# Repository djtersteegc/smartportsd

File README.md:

A couple PCB's I've designed to run the SmartportSD FAT code from Katherine Stark (based on the work of Robert Justice and Andrea Ottaviani) allowing you to connect a 32MB ProDOS partition to your SmartPort enabled Apple II (IIc, IIc+, IIgs). If you have a Apple IIe, solutions like a SoftSP card with you Disk II card, or something like Brad Bell's [SmartDiskII](https://github.com/btb/SmartDiskII) card will also allow hookup and usage. Yes, it works with Total Replay.

# SmartportSD Nano Shield

This is my original design.  Works best with a Duo Disk cable, but has a header to wire up a custom cable if needed.  All through hold modules, super easy build. I added some additional LED's to indicate which of the four ProDOS partitions is currently loaded.

See the [Nano Shield page](smartportsd-nano-shield/README.md) for BOM and assembly instructions.

# SmartportSD SMD

This one is a bit more of an advanced build and is based off my [Tapecart SD](https://github.com/djtersteegc/tapecart-sd-vertical) design I did for the Commodore 64. Uses a full size SD card for ease of handling and plugs in directly to the back of an Apple IIc/c+/gs.  There is a lightpipe for the activity LED and the narrow case design allows plenty of clearance for the bulkiest composite video connectors I could find in my collection.

See the [SMD page](smartport-smd/README.md) for BOM and assembly instructions.

# Getting a Board

If I have extra PCB's, they will be listed on Tindie.

https://www.tindie.com/products/tersteeg/smartportsd-apple-ii-pcb/

Otherwise, you can download the gerbers and use your favorite fab (JLCPCB, PCBWay, etc.) to make your own batch.

# Acknowledgements

Robert Justice for his original SmartPortCFA project http://www.users.on.net/~rjustice/SmartportCFA/SmartportCFA.htm

Andrea Ottaviani for his Arduino/SD port of Robert's work http://www.users.on.net/~rjustice/SmartportCFA/SmartportSD.htm

Katherine Stark for adding FAT support to Andrea's work to make it easier to manage the partitions on the SD card. https://gitlab.com/nyankat/smartportsd

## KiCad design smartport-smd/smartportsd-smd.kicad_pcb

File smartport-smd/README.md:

# BOM

There's an interactive BOM [here](https://djtersteegc.github.io/smartportsd/ibom-smd-v1.1.html), and CSV version with footprint info [here](https://djtersteegc.github.io/smartportsd/bom-smd-v1.1.csv). The interactive one is super useful when placing the SMD components.

C5 is an optional bulk capacitor for the 5V power rail near the MCU.  In my experience building these it is not needed.

The SD card connector is commonly available from several different Chinese suppliers and often called "long body", "non popping", or "push pull" on AliExpress or eBay.

https://www.aliexpress.us/item/3256805779248826.html

Here's some links on LCSC.

https://www.lcsc.com/product-detail/SD-Card-Connectors_Hanbo-Electronic-SD-112_C961673.html

https://www.lcsc.com/product-detail/SD-Card-Connectors_XUNPU-SD-102_C266602.html

https://www.lcsc.com/product-detail/SD-Card-Connectors_Megastar-ZX-SD-282-8Y_C7419835.html

It should also cross with a Wurth 693063010911 or AMP GSD090012SEU if you want something domestically.

The pins for the DB19 connector can be purchased from this seller on AliExpress,  https://www.aliexpress.us/item/3256802431271655.html Ideally I would have used the "PCB Plug" model if they stocked them which are similar to the TE/AMP 5-745287-4 model mozzwald used on the [FujiApple DB19 to IDC20 adapters](https://github.com/FujiNetWIFI/fujinet-hardware/tree/master/AppleII/DB-19M-Adapter), but these are much more cost effective and work just as well once assembled.

# Case

The case was created in DesignSpark and the design file is available if you would like to modify it further.

There is a single light pipe that should be printed in transparent material, or you can just leave it off completely. The case is designed to be printed at 0.2mm layer heights and assembled with two M2.5x14mm screws through the connector body and two M2.5 nuts pushed into either the handle or lid.

# Assembly

Assemble all the SMD components.  I use solder paste hand applied with a pneumatic dispenser and then finish on a hot plate. But you can also hand solder, use hot air, or even order a stencil for paste application and use a proper reflow oven. I use a red LED for the activity indicator. Make sure to observe polarity with the green stripe on the LED to the right matching the white stripe on the PCB silkscreen.

For the ATMEGA328P chip I did use part of stencil I had from a previous project with the same footprint, or you can buy one from [Amazon](https://www.amazon.com/Proto-Advantage-PA0091-S-TQFP-32-LQFP-32-Stainless/dp/B09886QDY9/ref=sr_1_3). Cheaper than ordering a whole stencil from somewhere like JLCPCB once you factor in shipping costs.

Do NOT install the 2x3 ICSP pin header at J2.  I would recommend flashing the firmware at this point to do basic checks since it's easier to do board rework before you install the DB19 pins.

To install the connector, first take your printed DB19 shell and use a 1.0mm and 2.0mm drill bit to properly size the holes.  I use a cut down DB25 connector to hold the pins straight while soldering. It also makes a nice way to hold everything in a vise.

Insert the pins and case shell through the case back and assemble with short M2.5 screws.  Tighten the screws gently so you can still slide out the case in the future if needed and then solder the pins. Ensure the tops of all the pins are even and the bottom of the solder cup on the pins should be close to even with the PCB.

When complete it should look something like this when slid out of the case.

Press the light pipe into the LED opening with the lip side facing up and then slide the board in. If you can't slide the PCB under the light pipe, it is installed upside down.  The side mounted LED's should keep the light pipe from falling out, even if it isn't a tight friction fit in the openings.

# Firmware Flashing

The ATmega328P is the same used on an Arduino Uno/Nano/Micro, but lacks the necessary bootloader firmware and serial interfaces to flash via the Arduino IDE or programs like XLoader. You could program the chip before installing it with something like a [TL866/T48](TL866/T48) and a [TQFP32 to DIP 32 adapter](https://www.aliexpress.us/item/2251832227450089.html), but I prefer to just use a cheap [UBSASP](https://www.aliexpress.us/item/2251832600419163.html) and [avrdude](https://github.com/avrdudes/avrdude). Make sure you get a 10 pin to 8 pin adapter with the USBASP if it isn't natively an 8 pin model.

Since you didn't solder the 2x3 pin header on the ICSP port J2, you will need to hold the header pins at an angle in the holes to make contact while you run avrdude.  If you're feeling fancy, you could spring for a [2x3 double row 2.54mm test clip](https://www.aliexpress.us/item/3256805646654844.html) or [handheld pogo pin probe](https://www.aliexpress.us/item/3256805545980544.html).  The cheap angle method works fine for me.

Since this model doesn't have the extra LED's to show the active partition, the firmware used is Katherine's standard version from https://gitlab.com/nyankat/smartportsd.  

In my [firmware](firmware) directory there are couple of Windows scripts and a precompiled version of the SmartportSD firmware.

First you to need to setup your ATMega328p with the correct fuse setting so it uses the external 16 MHz crystal, same as an Arduino board. **burn-328p-fuses.cmd** executes the following:

`avrdude -c usbasp -p m328p -B 125kHz -U lfuse:w:0xFF:m -U hfuse:w:0xDE:m -U efuse:w:0x05:m`

Next flash SmartportSD-1.15.ino.with_bootloader.standard.hex with **flash-smartportsd.cmd** that executes:

`avrdude -c usbasp -p m328p -u -U flash:w:SmartportSD-1.15.ino.with_bootloader.standard.hex`

Plug into your Apple II and enjoy! 

# Getting a Board

If you are in the US, PCB's are available from my Tindie store, https://www.tindie.com/products/tersteeg/smartportsd-apple-ii-pcb/

Otherwise, you can grab the [gerbers](gerbers) and order from your favorite PCB fab.

# PCB Revisions

### Version 1.0

Worked but since it was pertty much a 1:1 copy of my TapecartSD base PCB, was just a little to wide to clear the composite video connector on an Apple IIc once cased.

### Versions 1.1 (Current)

Board was narrowed to allow needed clearance on IIc/c+ models.

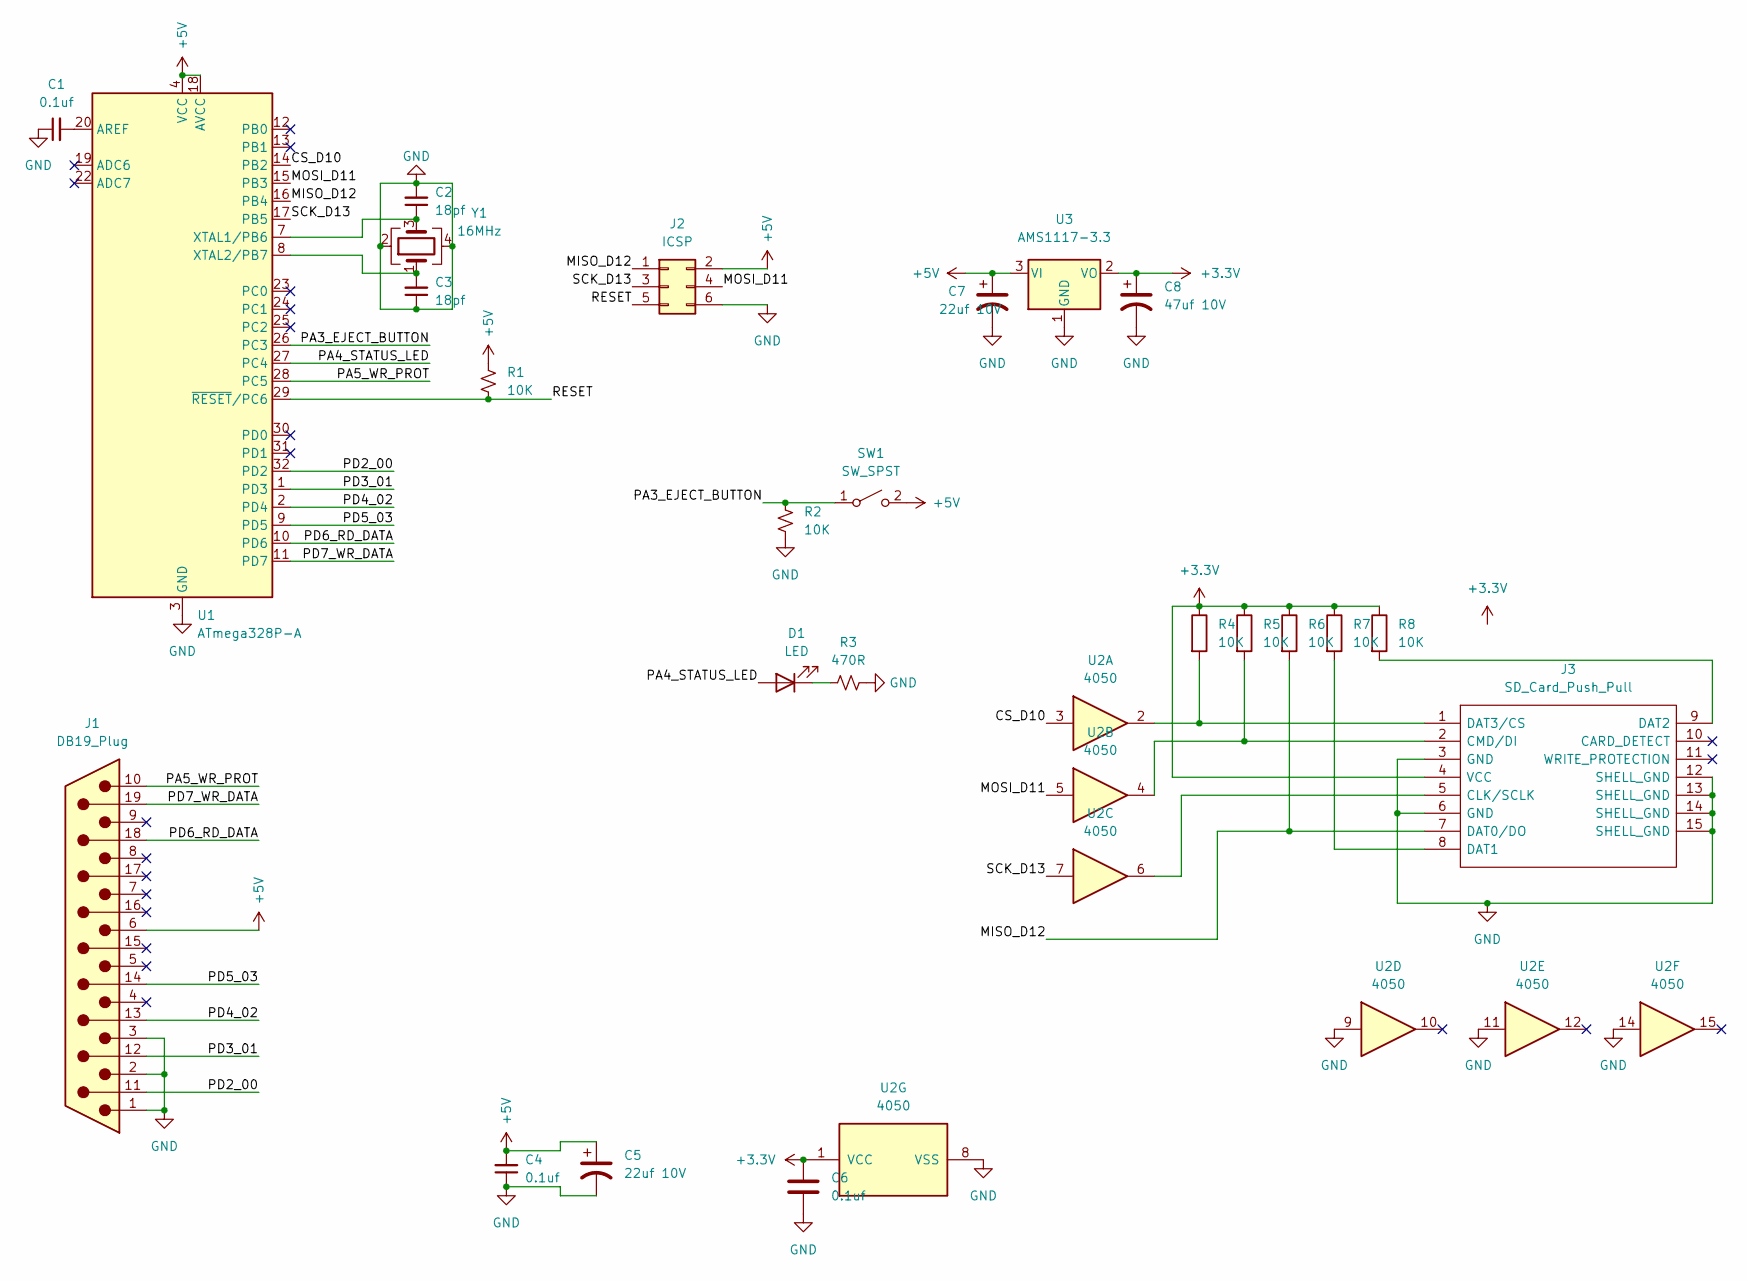
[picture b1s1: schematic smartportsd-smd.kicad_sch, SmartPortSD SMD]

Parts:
C1, C4, C6: 0.1uf; C_0805_2012Metric_Pad1.18x1.45mm_HandSolder
C2, C3: 18pf; C_0805_2012Metric_Pad1.18x1.45mm_HandSolder
C5, C7: 22uf 10V; CP_EIA-3216-18_Kemet-A_Pad1.58x1.35mm_HandSolder
C8: 47uf 10V; CP_EIA-3528-12_Kemet-T_Pad1.50x2.35mm_HandSolder
D1: LED; 1204 Side Emitting LED
J1: DB19_Plug; DSUB-19_Male_Vertical_P2.77x2.84mm_Narrow_MountingHoles
J2: ICSP; IDC-Header_2x03_P2.54mm_Vertical
J3: SD_Card_Push_Pull; 2041021-3_2; Manufacturer_Part_Number 2041021-3; Mouser Part Number 571-2041021-3
R1, R2, R4, R5, R6, R7, R8: 10K; R_0805_2012Metric_Pad1.20x1.40mm_HandSolder
R3: 470R; R_0805_2012Metric_Pad1.20x1.40mm_HandSolder
SW1: SW_SPST; SW_Push_SPST_NO_Alps_SKRK
U1: ATmega328P-A; TQFP-32_7x7mm_P0.8mm
U2: 4050; SOIC-16_3.9x9.9mm_P1.27mm
U3: AMS1117-3.3; SOT-223-3_TabPin2
Y1: 16MHz; Crystal_SMD_3225-4Pin_3.2x2.5mm_HandSoldering

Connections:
+3.3V: C6.2, C8.1, J3.4 (VCC), R4.1, R5.1, R6.1, R7.1, R8.1, U2.1 (VCC), U3.2 (VO)
+5V: C4.2, C5.1, C7.1, J1.6, J2.2, R1.1, SW1.2 (B), U1.4 (VCC), U1.6 (VCC), U1.18 (AVCC), U3.3 (VI)
/CS_D10: U1.14 (PB2), U2.3
/MISO_D12: J2.1, J3.7 (DAT0/DO), R6.2, U1.16 (PB4)
/MOSI_D11: J2.4, U1.15 (PB3), U2.5
/PA3_EJECT_BUTTON: R2.1, SW1.1 (A), U1.26 (PC3)
/PA4_STATUS_LED: D1.2 (A), U1.27 (PC4)
/PA5_WR_PROT: J1.10, U1.28 (PC5)
/PD2_00: J1.11, U1.32 (PD2)
/PD3_01: J1.12, U1.1 (PD3)
/PD4_02: J1.13, U1.2 (PD4)
/PD5_03: J1.14, U1.9 (PD5)
/PD6_RD_DATA: J1.18, U1.10 (PD6)
/PD7_WR_DATA: J1.19, U1.11 (PD7)
/RESET: J2.5, R1.2, U1.29 (~RESET/PC6)
/SCK_D13: J2.3, U1.17 (PB5), U2.7
GND: C1.1, C2.2, C3.1, C4.1, C5.2, C6.1, C7.2, C8.2, J1.1, J1.2, J1.3, J2.6, J3.3 (GND), J3.6 (GND), J3.12 (SHELL_GND), J3.13 (SHELL_GND), J3.14 (SHELL_GND), J3.15 (SHELL_GND), R2.2, R3.2, U1.3 (GND), U1.5 (GND), U1.21 (GND), U2.8 (VSS), U2.9, U2.11, U2.14, U3.1 (GND), Y1.2, Y1.4
unnamed: D1.1 (K), R3.1
unnamed: J3.5 (CLK/SCLK), U2.6
unnamed: J3.2 (CMD/DI), R5.2, U2.4
unnamed: J3.8 (DAT1), R7.2
unnamed: J3.9 (DAT2), R8.2
unnamed: J3.1 (DAT3/CS), R4.2, U2.2
unnamed: C1.2, U1.20 (AREF)
unnamed: C2.1, U1.7 (XTAL1/PB6), Y1.3
unnamed: C3.2, U1.8 (XTAL2/PB7), Y1.1

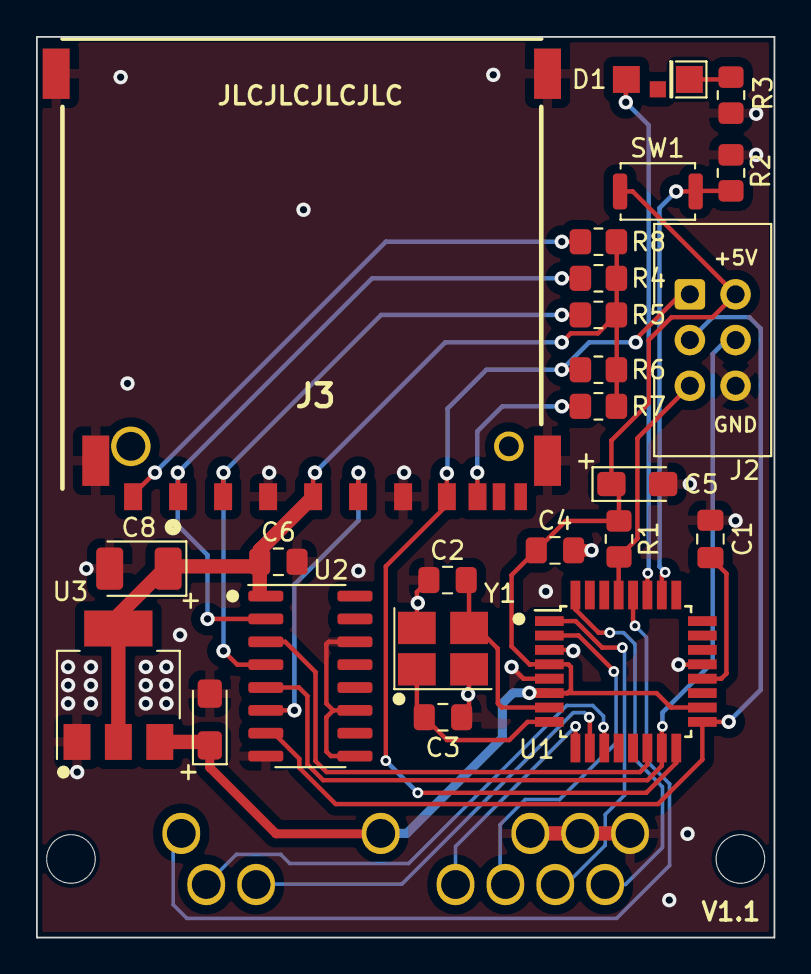
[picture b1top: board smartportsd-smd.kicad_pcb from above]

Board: 2 copper layers, 41.0 x 50.0 mm, 25 parts (1 on the bottom side), 26 nets.

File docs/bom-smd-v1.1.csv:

"#","Reference","Qty","Value","Footprint","DNP"
"1","C1, C4, C6","3","0.1uf","Capacitor_SMD:C_0805_2012Metric_Pad1.18x1.45mm_HandSolder",""
"2","C2, C3","2","18pf","Capacitor_SMD:C_0805_2012Metric_Pad1.18x1.45mm_HandSolder",""
"3","C5, C7","2","22uf 10V","Capacitor_Tantalum_SMD:CP_EIA-3216-18_Kemet-A_Pad1.58x1.35mm_HandSolder",""
"4","C8","1","47uf 10V","Capacitor_Tantalum_SMD:CP_EIA-3528-12_Kemet-T_Pad1.50x2.35mm_HandSolder",""
"5","D1","1","LED","Tersteeg:1204 Side Emitting LED",""
"6","J1","1","DB19_Plug","Tersteeg:DSUB-19_Male_Vertical_P2.77x2.84mm_Narrow_MountingHoles",""
"7","J2","1","ICSP","Connector_IDC:IDC-Header_2x03_P2.54mm_Vertical",""
"8","J3","1","SD_Card_Push_Pull","TE SD Card 2041021-3:2041021-3_2",""
"9","R1, R2, R4, R5, R6, R7, R8","7","10K","Resistor_SMD:R_0805_2012Metric_Pad1.20x1.40mm_HandSolder",""
"10","R3","1","470R","Resistor_SMD:R_0805_2012Metric_Pad1.20x1.40mm_HandSolder",""
"11","SW1","1","SW_SPST","Button_Switch_SMD:SW_Push_SPST_NO_Alps_SKRK",""
"12","U1","1","ATmega328P-A","Package_QFP:TQFP-32_7x7mm_P0.8mm",""
"13","U2","1","4050","Package_SO:SOIC-16_3.9x9.9mm_P1.27mm",""
"14","U3","1","AMS1117-3.3","Package_TO_SOT_SMD:SOT-223-3_TabPin2",""
"15","Y1","1","16MHz","Crystal:Crystal_SMD_3225-4Pin_3.2x2.5mm_HandSoldering",""

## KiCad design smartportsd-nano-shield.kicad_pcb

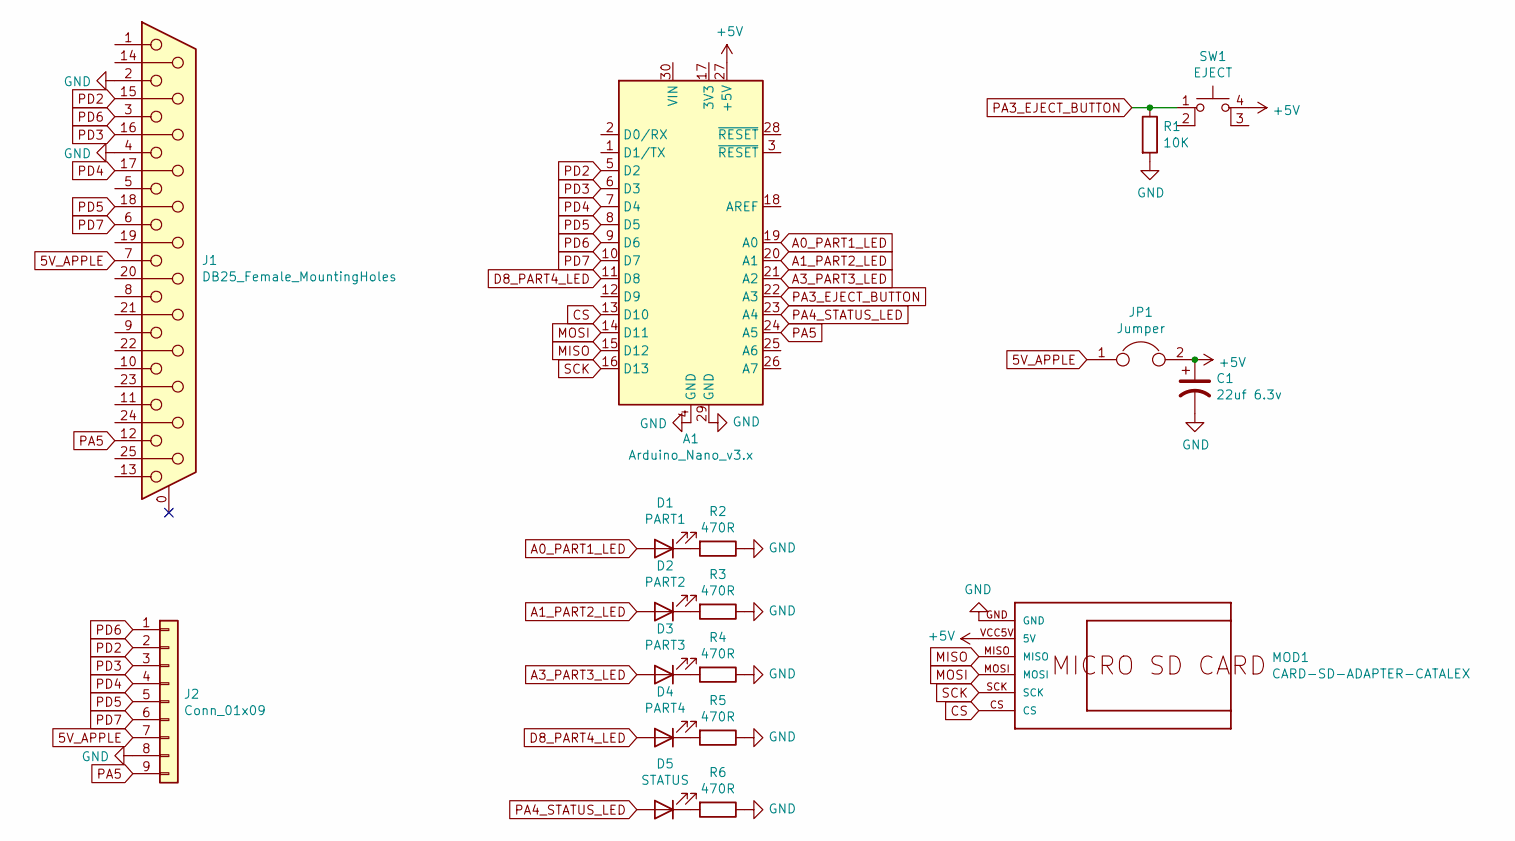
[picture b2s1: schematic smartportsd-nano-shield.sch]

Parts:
A1: Arduino_Nano_v3.x; Arduino_Nano
C1: 22uf 6.3v; CP_Radial_D4.0mm_P1.50mm
D1: PART1; LED_D5.0mm
D2: PART2; LED_D5.0mm
D3: PART3; LED_D5.0mm
D4: PART4; LED_D5.0mm
D5: STATUS; LED_D5.0mm
J1: DB25_Female_MountingHoles; DSUB-25_Female_Horizontal_P2.77x2.84mm_EdgePinOffset7.70mm_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
J2: Conn_01x09; PinHeader_1x09_P2.54mm_Horizontal
JP1: Jumper; PinHeader_1x02_P2.54mm_Vertical
MOD1: CARD-SD-ADAPTER-CATALEX; Catalex-MicroSD-Card-Down
R1: 10K; R_Axial_DIN0207_L6.3mm_D2.5mm_P7.62mm_Horizontal
R2, R3, R4, R5, R6: 470R; R_Axial_DIN0207_L6.3mm_D2.5mm_P7.62mm_Horizontal
SW1: EJECT; SW_TH_Tactile_Omron_B3F-10xx

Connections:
5V_APPLE: J1.7, J2.7, JP1.1
+5V: A1.27 (+5V), C1.1, JP1.2, MOD1.VCC5V (5V), SW1.4 (A)
A0_PART1_LED: A1.19 (A0), D1.2 (A)
A1_PART2_LED: A1.20 (A1), D2.2 (A)
A3_PART3_LED: A1.21 (A2), D3.2 (A)
CS: A1.13 (D10), MOD1.CS
D8_PART4_LED: A1.11 (D8), D4.2 (A)
GND: A1.4 (GND), A1.29 (GND), C1.2, J1.2, J1.4, J2.8, MOD1.GND, R1.2, R2.1, R3.1, R4.1, R5.1, R6.1
MISO: A1.15 (D12), MOD1.MISO
MOSI: A1.14 (D11), MOD1.MOSI
unnamed: D1.1 (K), R2.2
unnamed: D2.1 (K), R3.2
unnamed: D3.1 (K), R4.2
unnamed: D4.1 (K), R5.2
unnamed: D5.1 (K), R6.2
PA3_EJECT_BUTTON: A1.22 (A3), R1.1, SW1.1
PA4_STATUS_LED: A1.23 (A4), D5.2 (A)
PA5: A1.24 (A5), J1.12, J2.9
PD2: A1.5 (D2), J1.15, J2.2
PD3: A1.6 (D3), J1.16, J2.3
PD4: A1.7 (D4), J1.17, J2.4
PD5: A1.8 (D5), J1.18, J2.5
PD6: A1.9 (D6), J1.3, J2.1
PD7: A1.10 (D7), J1.6, J2.6
SCK: A1.16 (D13), MOD1.SCK

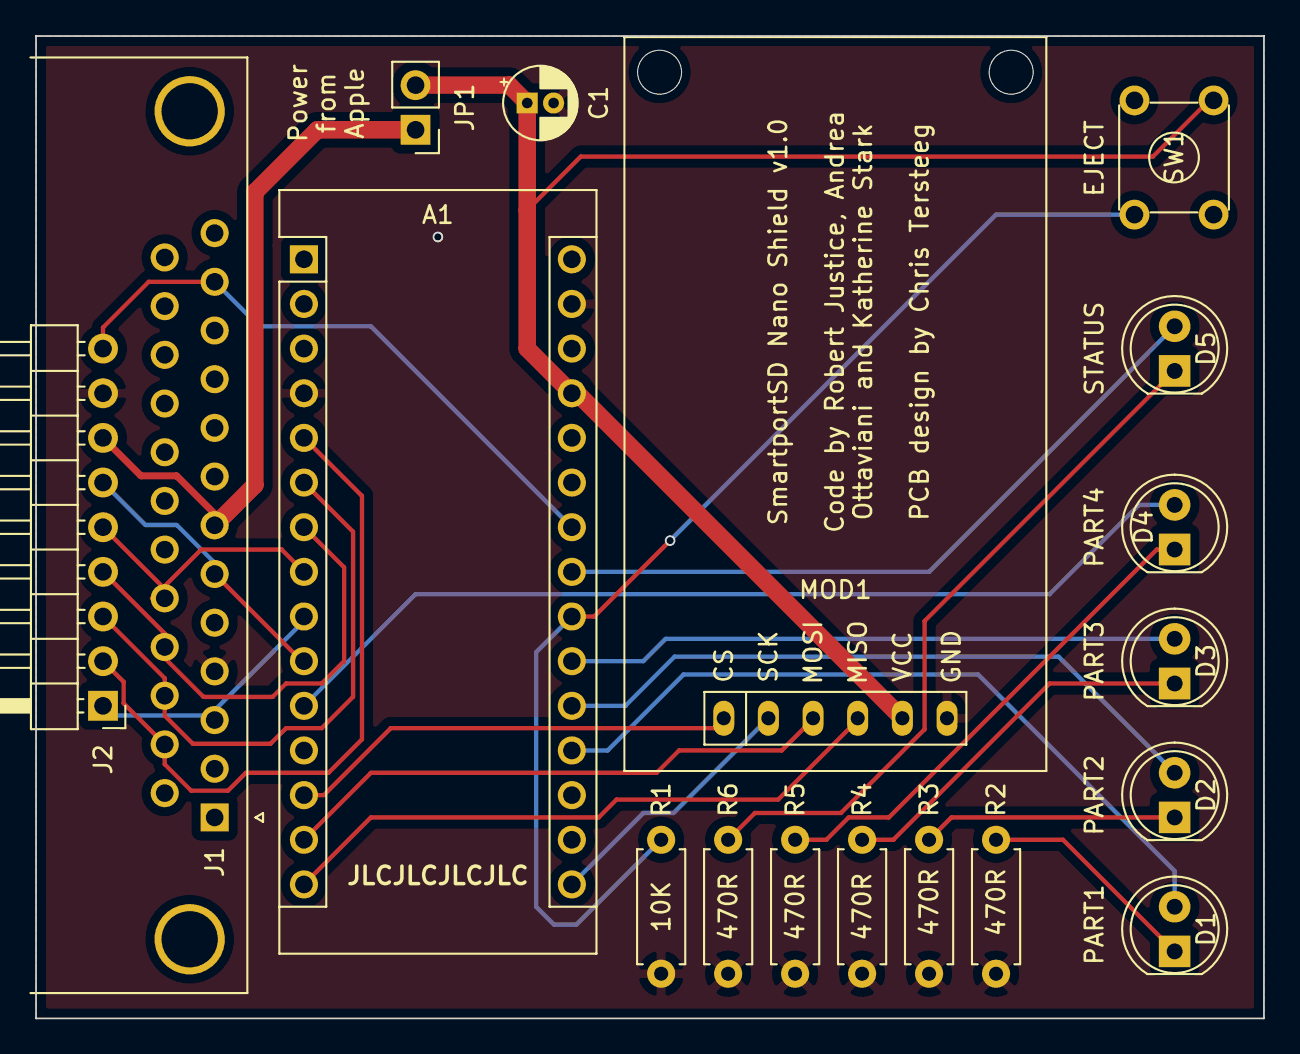
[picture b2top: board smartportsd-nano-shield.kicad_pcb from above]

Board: 2 copper layers, 69.8 x 55.9 mm, 18 parts (0 on the bottom side), 25 nets.

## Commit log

2021-02-28 Initial version sent to JCL
2021-03-31 Add some docs
2021-03-31 Fix links
2021-04-01 Add Tindie link
2022-10-05 Add enclosure files
2024-01-07 Restructure repo for multiple PCB projects
2024-01-07 Add SMD V1.1 PCB
2024-01-08 Initial round of updated docs for the SMD version
2024-01-08 Update docs
2024-01-08 Fix misnamed BOM file
2024-01-08 Fix broken image
2025-03-01 Add IDC-20 pin mappings to docs
